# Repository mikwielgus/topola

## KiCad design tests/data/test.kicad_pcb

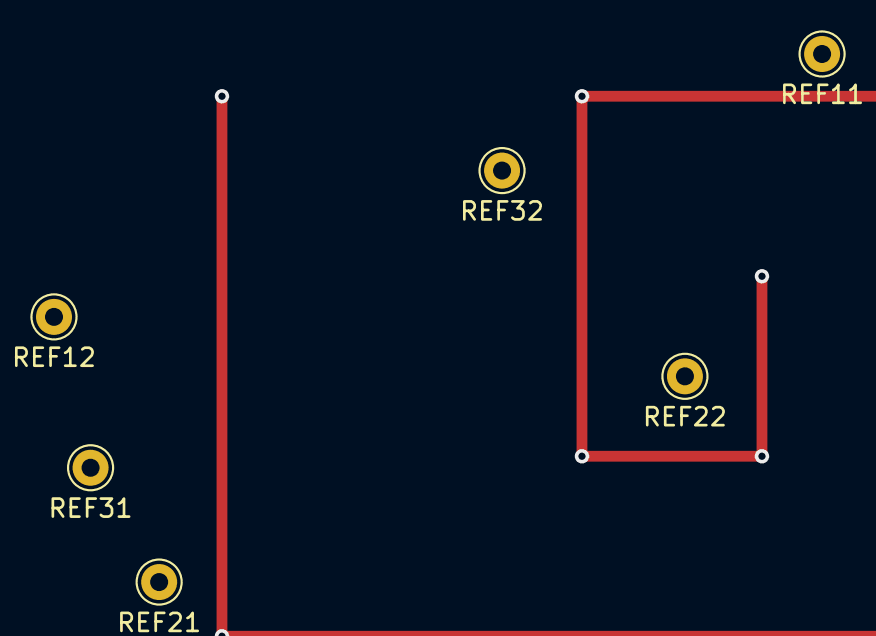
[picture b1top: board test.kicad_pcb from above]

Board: 2 copper layers, 6 parts (0 on the bottom side), 3 nets.

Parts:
REF11, REF12, REF21, REF22, REF31, REF32: Pin_D1.0mm_L10.0mm

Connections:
1: REF11.1, REF12.1
2: REF21.1, REF22.1
3: REF31.1, REF32.1

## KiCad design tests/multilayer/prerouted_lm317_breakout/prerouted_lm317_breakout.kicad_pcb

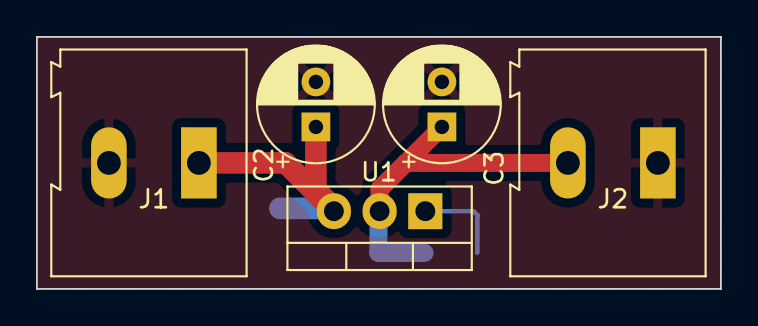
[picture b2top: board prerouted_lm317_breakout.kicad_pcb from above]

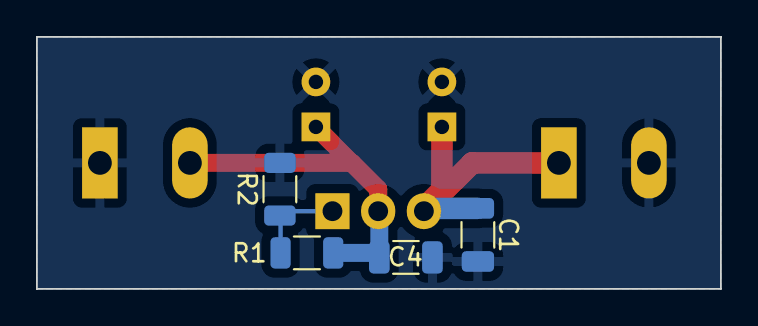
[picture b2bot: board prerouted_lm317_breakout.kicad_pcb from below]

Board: 2 copper layers, 38.0 x 14.0 mm, 9 parts (4 on the bottom side), 4 nets.

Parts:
C1, C4: 100n; C_1206_3216Metric
C2, C3: 470u; CP_Radial_D6.3mm_P2.50mm
J1, J2: Screw_Terminal_01x02; TerminalBlock_Altech_AK300-2_P5.00mm
R1: 240; R_1206_3216Metric
R2: 750; R_1206_3216Metric
U1: LM317_TO-220; TO-220-3_Vertical

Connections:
/adj: R1.2, R2.1, U1.1 (ADJ)
/wejście: C1.1, C2.1, J1.1, U1.3 (VI)
/wyjście: C3.1, C4.1, J2.2, R1.1, U1.2 (VO)
GND: C1.2, C2.2, C3.2, C4.2, J1.2, J2.1, R2.2

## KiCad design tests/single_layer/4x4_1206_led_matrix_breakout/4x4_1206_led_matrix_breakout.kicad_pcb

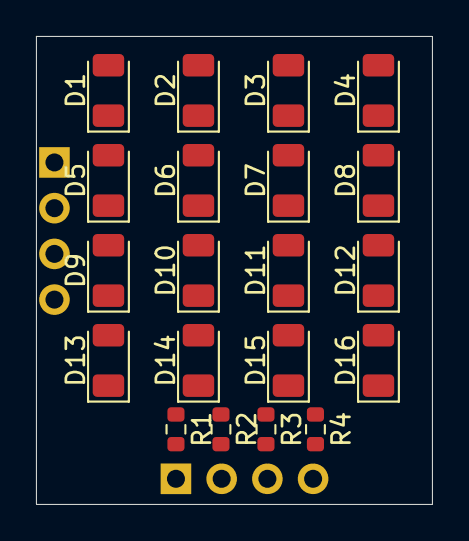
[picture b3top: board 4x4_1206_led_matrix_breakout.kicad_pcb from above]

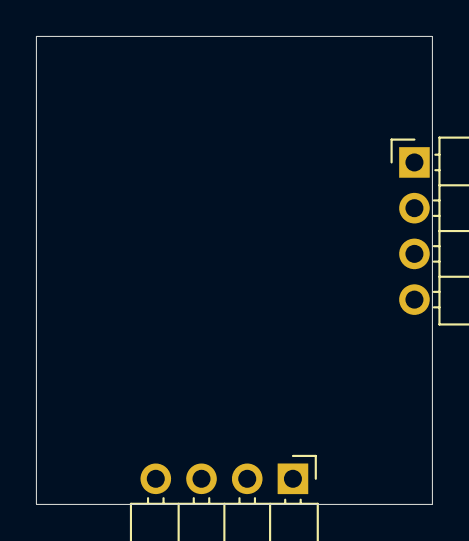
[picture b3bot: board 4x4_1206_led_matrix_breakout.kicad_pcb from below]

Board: 2 copper layers, 22.0 x 26.0 mm, 22 parts (2 on the bottom side), 12 nets, no tracks yet.

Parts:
D1, D2, D3, D4, D5, D6, D7, D8, D9, D10, D11, D12, D13, D14, D15, D16: LED; LED_1206_3216Metric
J1, J2: Conn_01x04_Pin; PinHeader_1x04_P2.54mm_Horizontal
R1, R2, R3, R4: 220; R_0603_1608Metric

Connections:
/COL0: D1.1 (K), D5.1 (K), D9.1 (K), D13.1 (K), R1.1
/COL1: D2.1 (K), D6.1 (K), D10.1 (K), D14.1 (K), R2.1
/COL2: D3.1 (K), D7.1 (K), D11.1 (K), D15.1 (K), R3.1
/COL3: D4.1 (K), D8.1 (K), D12.1 (K), D16.1 (K), R4.1
/ROW0: D1.2 (A), D2.2 (A), D3.2 (A), D4.2 (A), J1.1
/ROW1: D5.2 (A), D6.2 (A), D7.2 (A), D8.2 (A), J1.2
/ROW2: D9.2 (A), D10.2 (A), D11.2 (A), D12.2 (A), J1.3
/ROW3: D13.2 (A), D14.2 (A), D15.2 (A), D16.2 (A), J1.4
unnamed: J2.1, R1.2
unnamed: J2.2, R2.2
unnamed: J2.3, R3.2
unnamed: J2.4, R4.2

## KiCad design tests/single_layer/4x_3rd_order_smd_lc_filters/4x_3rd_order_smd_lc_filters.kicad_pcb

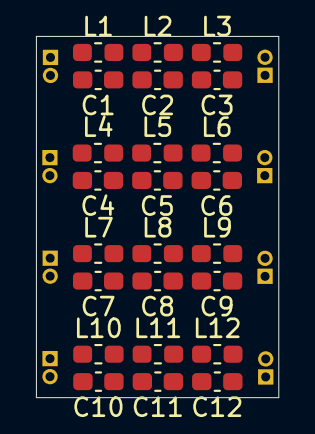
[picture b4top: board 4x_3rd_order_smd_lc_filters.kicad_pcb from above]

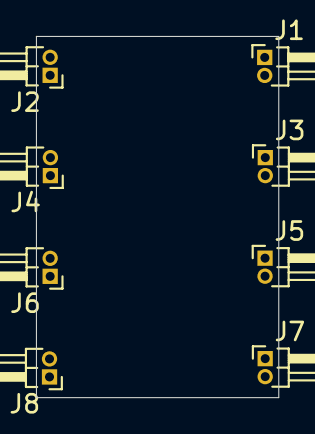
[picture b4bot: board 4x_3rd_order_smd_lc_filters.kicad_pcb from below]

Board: 2 copper layers, 13.5 x 20.1 mm, 32 parts (8 on the bottom side), 17 nets, no tracks yet.

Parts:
C1, C2, C3, C4, C5, C6, C7, C8, C9, C10, C11, C12: C; C_0603_1608Metric_Pad1.08x0.95mm_HandSolder
J1, J2, J3, J4, J5, J6, J7, J8: Conn_01x02_Męski; PinHeader_1x02_P1.00mm_Horizontal
L1, L2, L3, L4, L5, L6, L7, L8, L9, L10, L11, L12: L; L_0603_1608Metric_Pad1.05x0.95mm_HandSolder

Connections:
GND: C1.2, C2.2, C3.2, C4.2, C5.2, C6.2, C7.2, C8.2, C9.2, C10.2, C11.2, C12.2, J1.2, J2.2, J3.2, J4.2, J5.2, J6.2, J7.2, J8.2
unnamed: C1.1, L1.2, L2.1
unnamed: C2.1, L2.2, L3.1
unnamed: C4.1, L4.2, L5.1
unnamed: C5.1, L5.2, L6.1
unnamed: C7.1, L7.2, L8.1
unnamed: C8.1, L8.2, L9.1
unnamed: C10.1, L10.2, L11.1
unnamed: C11.1, L11.2, L12.1
unnamed: J1.1, L1.1
unnamed: C3.1, J2.1, L3.2
unnamed: J3.1, L4.1
unnamed: C6.1, J4.1, L6.2
unnamed: J5.1, L7.1
unnamed: C9.1, J6.1, L9.2
unnamed: J7.1, L10.1
unnamed: C12.1, J8.1, L12.2
